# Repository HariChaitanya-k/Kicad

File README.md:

Inverter folder contains all schematic and layout files and gerber folder

modefication1:Adding  a second, identical inverter stage so the board becomes a non-inverting buffer

modefication2:Move the LED so it lights when the output is low instead of high

modefication3:Re-route the whole board with the minimum clearance raised to 0.4 mm, as a cheaper fabricator might demand.

modefication4:4. Replace the trimpot with a two-pin header so the input comes only from outside, and shrink the
board as far as the DRC will let me.

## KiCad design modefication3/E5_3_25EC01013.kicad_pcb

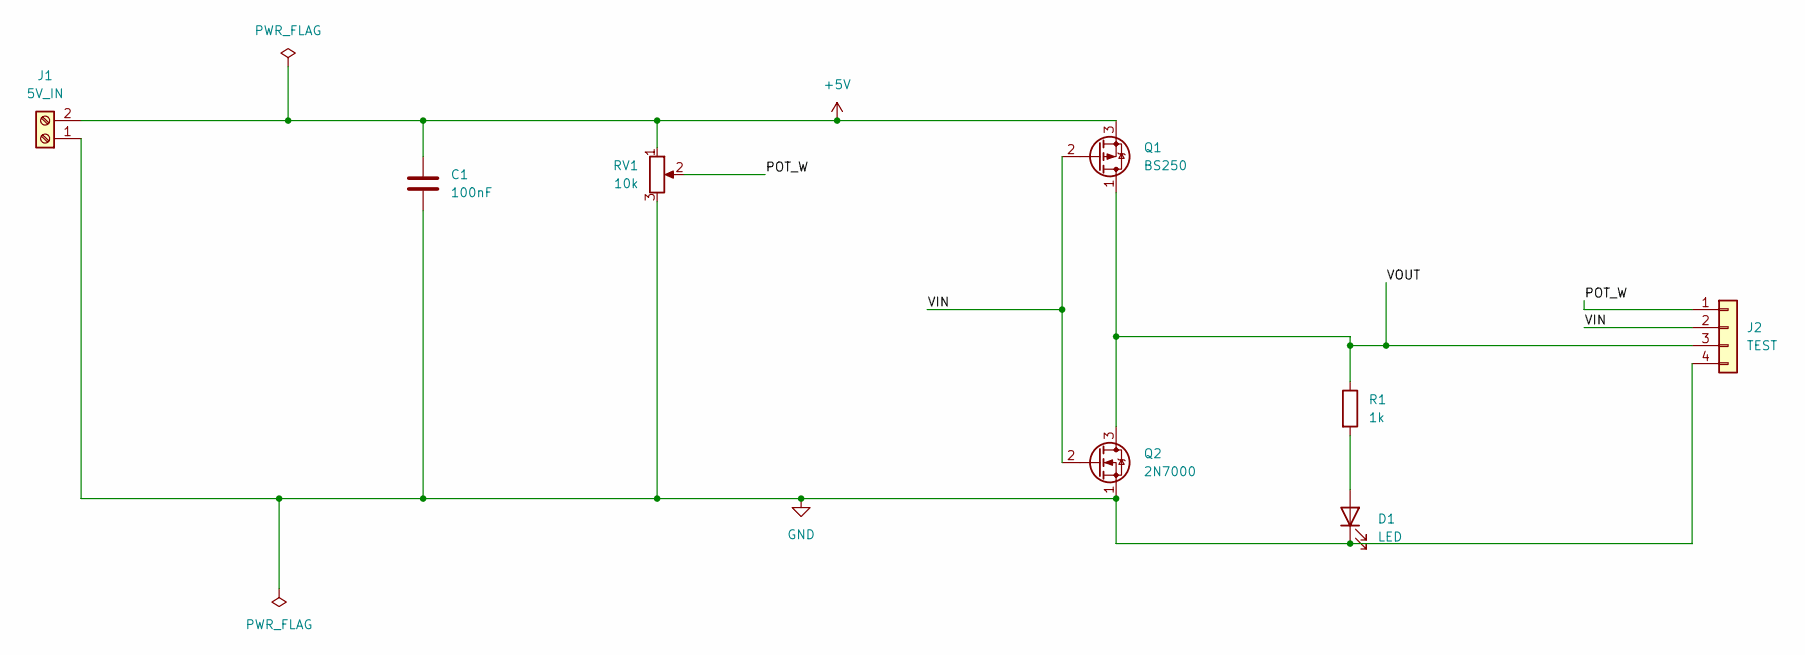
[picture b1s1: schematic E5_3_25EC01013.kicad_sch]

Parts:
C1: 100nF; C_Disc_D5.0mm_W2.5mm_P5.00mm
D1: LED; LED_D3.0mm
J1: 5V_IN; TerminalBlock_Phoenix_MKDS-1,5-2-5.08_1x02_P5.08mm_Horizont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
J2: TEST; PinHeader_1x04_P2.54mm_Vertical
Q1: BS250; TO-92_Inline_Wide
Q2: 2N7000; TO-92_Inline_Wide
R1: 1k; R_Axial_DIN0207_L6.3mm_D2.5mm_P10.16mm_Horizontal
RV1: 10k; Potentiometer_Bourns_3386P_Vertical

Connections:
+5V: C1.1, J1.2, Q1.3 (S), RV1.1
/POT_W: J2.1, RV1.2
/VIN: J2.2, Q1.2 (G), Q2.2 (G)
/VOUT: J2.3, Q1.1 (D), Q2.3 (D), R1.1
GND: C1.2, D1.1 (K), J1.1, J2.4, Q2.1 (S), RV1.3
unnamed: D1.2 (A), R1.2

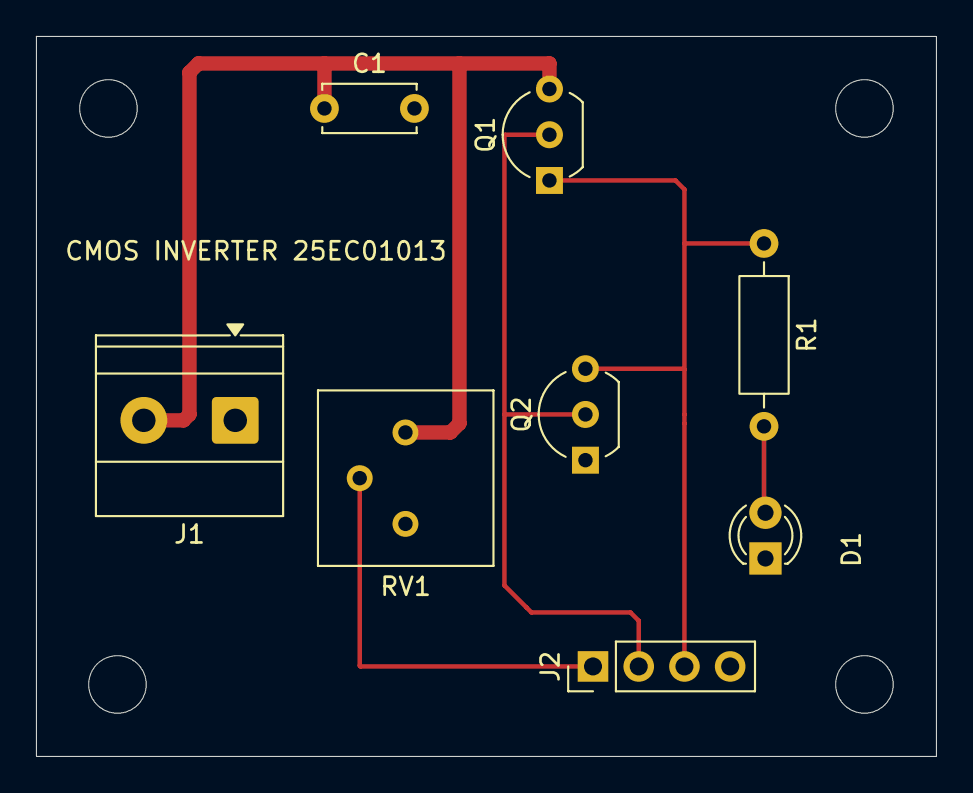
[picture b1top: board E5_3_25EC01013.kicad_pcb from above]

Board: 2 copper layers, 50.0 x 40.0 mm, 8 parts (0 on the bottom side), 6 nets.

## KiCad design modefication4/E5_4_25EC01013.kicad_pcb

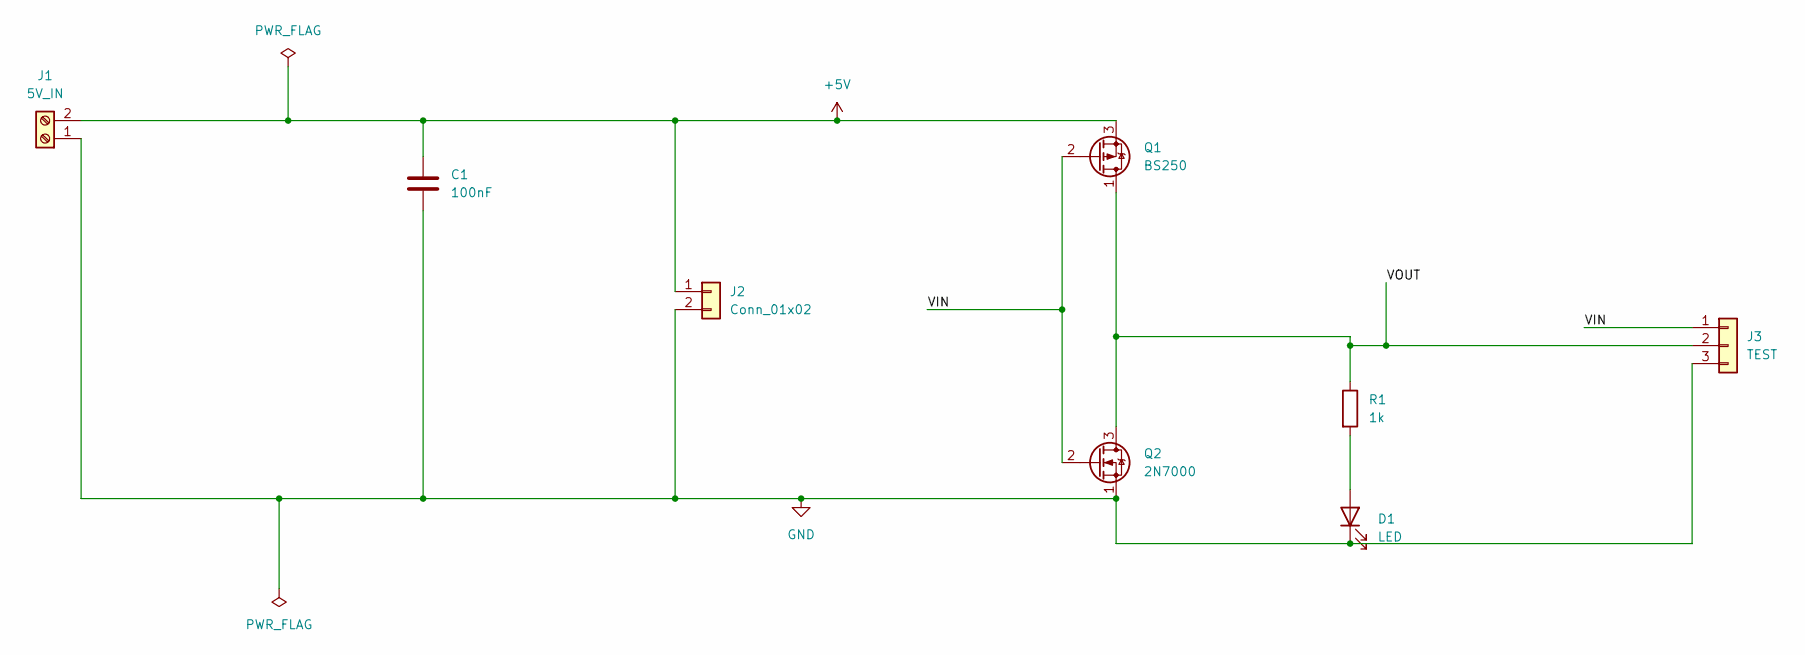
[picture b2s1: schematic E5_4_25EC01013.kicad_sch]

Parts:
C1: 100nF; C_Disc_D5.0mm_W2.5mm_P5.00mm
D1: LED; LED_D3.0mm
J1: 5V_IN; TerminalBlock_Phoenix_MKDS-1,5-2-5.08_1x02_P5.08mm_Horizont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
J2: Conn_01x02; PinHeader_1x02_P2.54mm_Vertical
J3: TEST; PinHeader_1x03_P2.54mm_Vertical
Q1: BS250; TO-92_Inline
Q2: 2N7000; TO-92_Inline
R1: 1k; R_Axial_DIN0207_L6.3mm_D2.5mm_P10.16mm_Horizontal

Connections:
+5V: C1.1, J1.2, J2.1, Q1.3 (S)
/VIN: J3.1, Q1.2 (G), Q2.2 (G)
/VOUT: J3.2, Q1.1 (D), Q2.3 (D), R1.1
GND: C1.2, D1.1 (K), J1.1, J2.2, J3.3, Q2.1 (S)
unnamed: D1.2 (A), R1.2

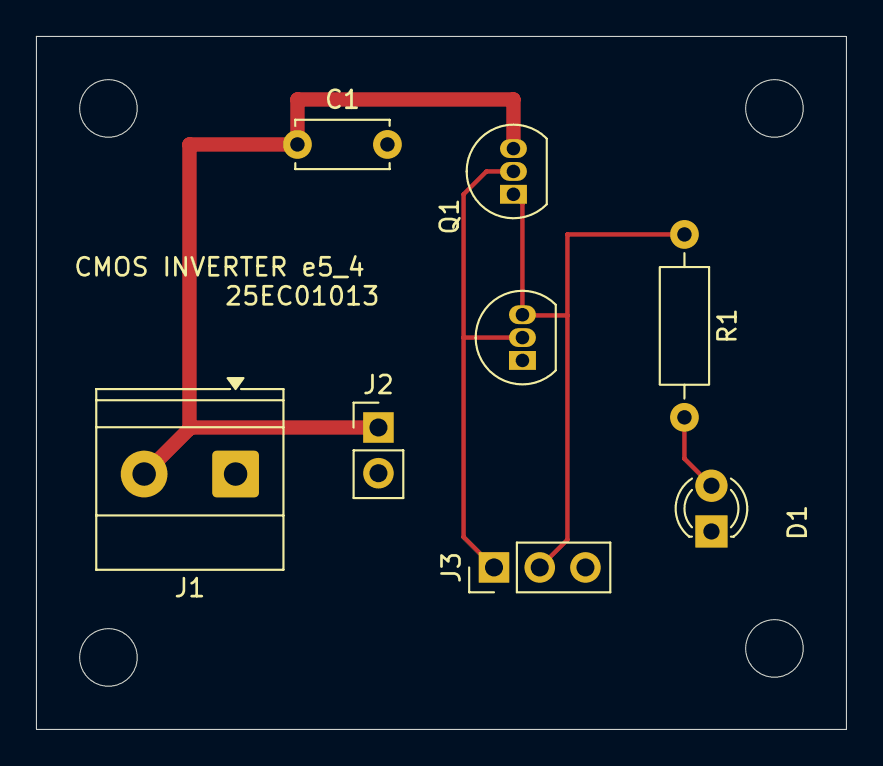
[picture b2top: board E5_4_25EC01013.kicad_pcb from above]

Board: 2 copper layers, 45.0 x 38.5 mm, 8 parts (0 on the bottom side), 5 nets.
